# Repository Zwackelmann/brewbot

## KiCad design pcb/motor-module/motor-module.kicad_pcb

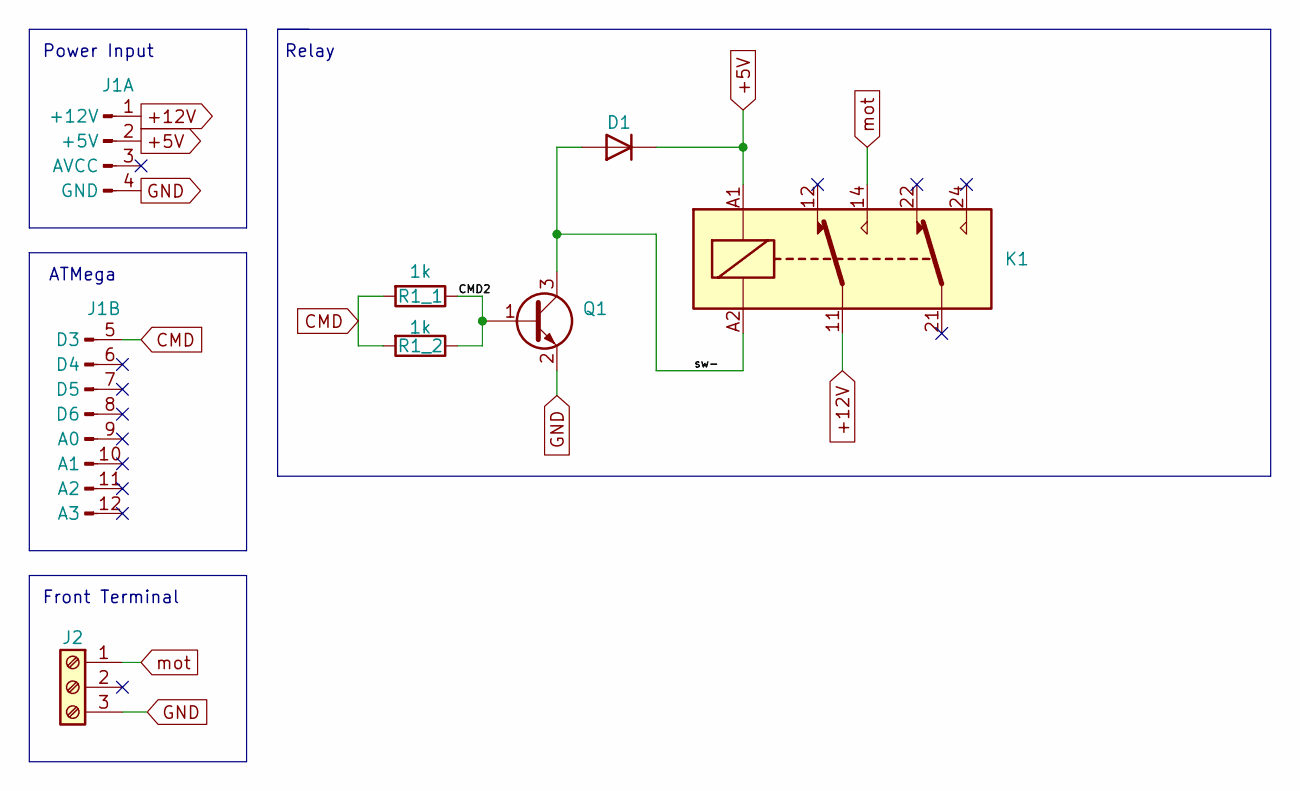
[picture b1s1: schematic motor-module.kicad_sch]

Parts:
D1: GS1A Gleichrichterdiode, 50 V, 1 A, DO-214AC/SMA; D_SMA
J1: Connector_male_4x8
J2: Screw_Terminal_01x03; Wago_734-163_1x03_P3.50mm_Horizontal
K1: AZ822-2C-5DSE Signal-Relais, 5 V DC, 2 A, 2 CO; Relay_DPDT_Finder_30.22
Q1: 2N 2222A SMD Bipolartransistor, NPN, 40V, 0,8A, 0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; SOT-23
R1_1, R1_2: 1k; R_0805_2012Metric

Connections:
+5V: D1.1 (K), J1.2 (+5V), K1.A1
+12V: J1.1 (+12V), K1.11
/CMD2: Q1.1 (B), R1_1.1, R1_2.1
/sw-: D1.2 (A), K1.A2, Q1.3 (C)
CMD: J1.5 (D3), R1_1.2, R1_2.2
GND: J1.4 (GND), J2.3, Q1.2 (E)
mot: J2.1, K1.14

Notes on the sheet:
ATMega
Power Input
Relay
Front Terminal

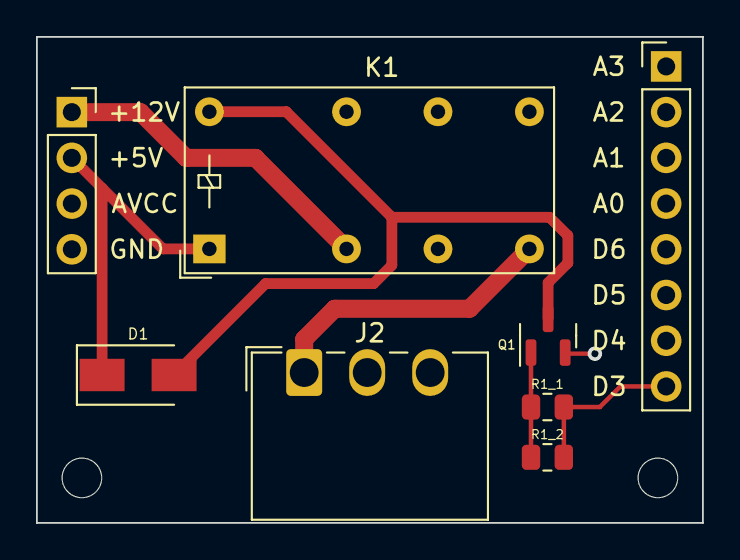
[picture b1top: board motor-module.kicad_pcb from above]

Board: 2 copper layers, 37.0 x 27.0 mm, 7 parts (0 on the bottom side), 7 nets.

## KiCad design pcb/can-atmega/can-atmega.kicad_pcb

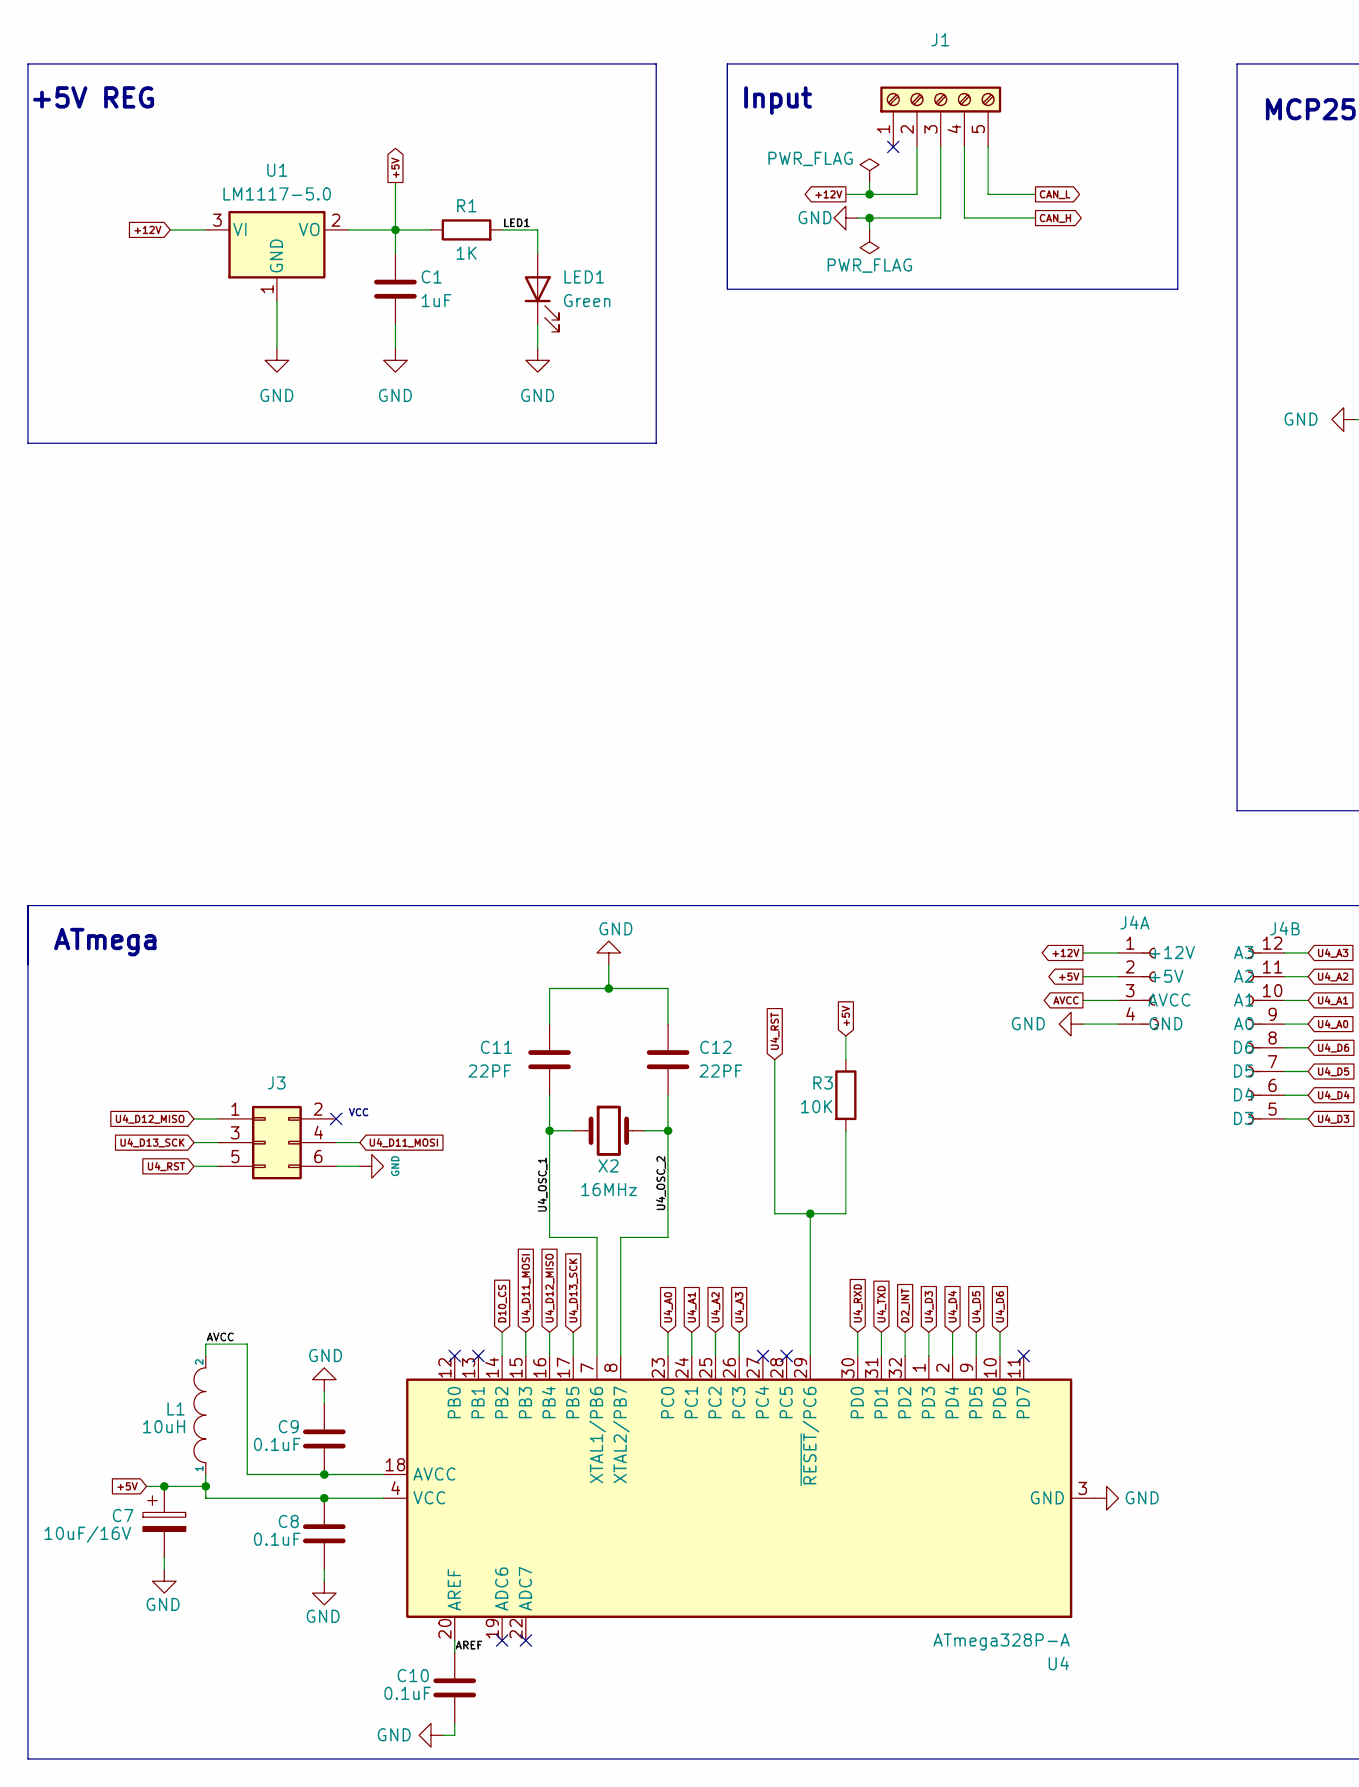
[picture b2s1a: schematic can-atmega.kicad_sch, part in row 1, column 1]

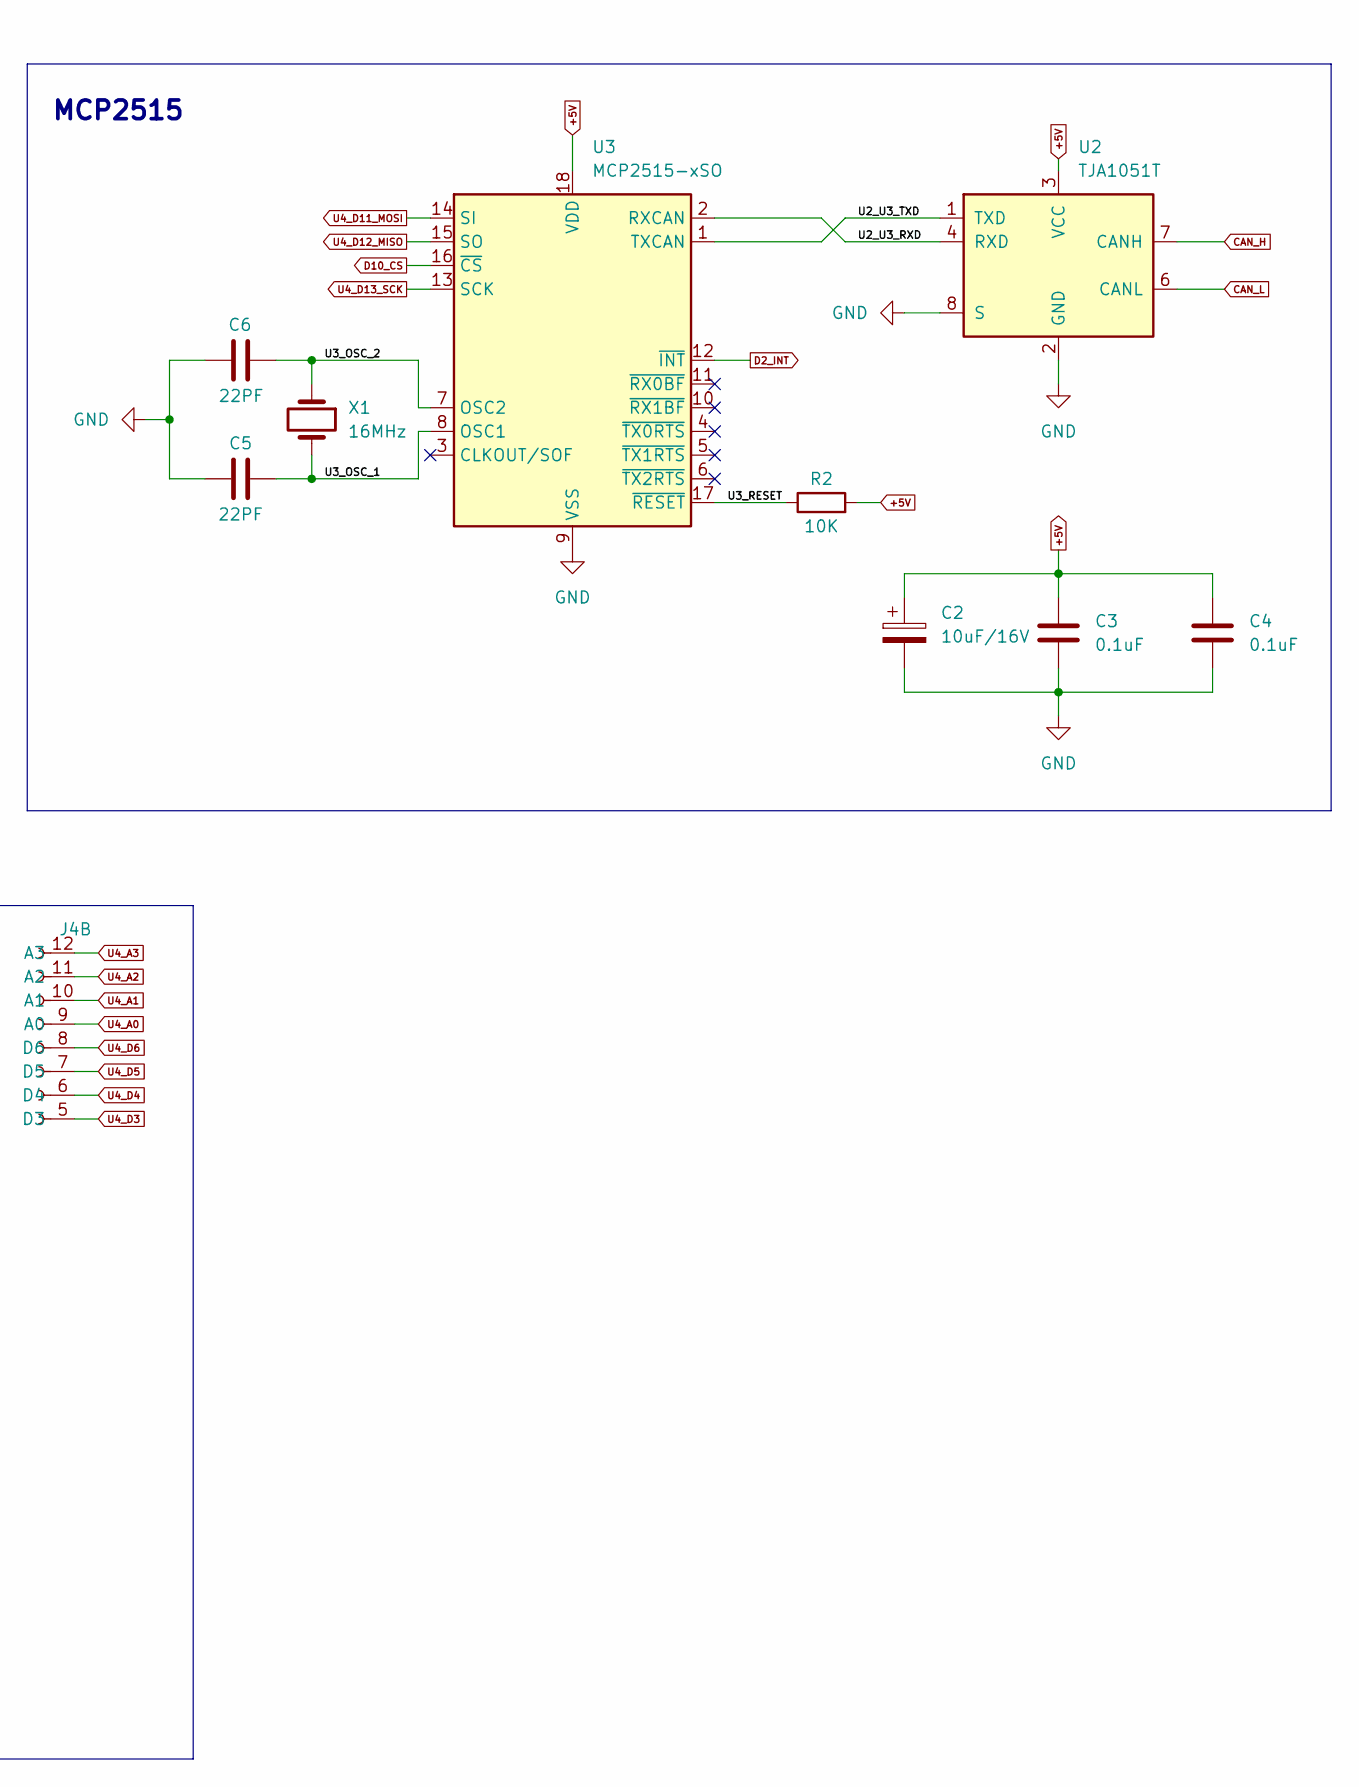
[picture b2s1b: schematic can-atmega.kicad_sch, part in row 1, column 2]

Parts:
C1: 1uF; C_1206_3216Metric
C2, C7: 10uF/16V; CP_EIA-3216-18_Kemet-A
C3, C4, C8, C9, C10: 0.1uF; C_1206_3216Metric
C5, C6, C11, C12: 22PF; C_1206_3216Metric
J1: Screw_Terminal_01x05; 4301207
J3: Conn_02x03_Odd_Even; IDC-Header_2x03_P2.54mm_Vertical
J4: Connector_female_4x8
L1: 10uH; L_Neosid_SMS-ME3010
LED1: Green; LED_0805_2012Metric
R1: 1K; R_0805_2012Metric
R2, R3: 10K; R_0805_2012Metric
U1: LM1117-5.0; SOT-223
U2: TJA1051T; SOIC-8_3.9x4.9mm_P1.27mm
U3: MCP2515-xSO; SOIC-18W_7.5x11.6mm_P1.27mm
U4: ATmega328P-A; TQFP-32_7x7mm_P0.8mm
X1, X2: 16MHz; Crystal_HC49-4H_Vertical

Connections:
+5V: C1.1, C2.1, C3.1, C4.1, C7.1, C8.1, J4.2 (+5V), L1.1, R1.1, R2.2, R3.1, U1.2 (VO), U1.4, U2.3 (VCC), U3.18 (VDD), U4.4 (VCC), U4.6 (VCC)
+12V: J1.2, J4.1 (+12V), U1.3 (VI)
/AREF: C10.2, U4.20 (AREF)
/LED1: LED1.2 (A), R1.2
/U2_U3_RXD: U2.4 (RXD), U3.2 (RXCAN)
/U2_U3_TXD: U2.1 (TXD), U3.1 (TXCAN)
/U3_OSC_1: C5.2, U3.8 (OSC1), X1.2
/U3_OSC_2: C6.2, U3.7 (OSC2), X1.1
/U3_RESET: R2.1, U3.17 (~RESET)
/U4_OSC_1: C11.1, U4.7 (XTAL1/PB6), X2.1
/U4_OSC_2: C12.2, U4.8 (XTAL2/PB7), X2.2
AVCC: C9.2, J4.3 (AVCC), L1.2, U4.18 (AVCC)
CAN_H: J1.4, U2.7 (CANH)
CAN_L: J1.5, U2.6 (CANL)
D2_INT: U3.12 (~INT), U4.32 (PD2)
D10_CS: U3.16 (~CS), U4.14 (PB2)
GND: C1.2, C2.2, C3.2, C4.2, C5.1, C6.1, C7.2, C8.2, C9.1, C10.1, C11.2, C12.1, J1.3, J3.6, J4.4 (GND), LED1.1 (K), U1.1 (GND), U2.2 (GND), U2.8 (S), U3.9 (VSS), U4.3 (GND), U4.5 (GND), U4.21 (GND)
U4_A0: J4.9 (A0), U4.23 (PC0)
U4_A1: J4.10 (A1), U4.24 (PC1)
U4_A2: J4.11 (A2), U4.25 (PC2)
U4_A3: J4.12 (A3), U4.26 (PC3)
U4_D3: J4.5 (D3), U4.1 (PD3)
U4_D4: J4.6 (D4), U4.2 (PD4)
U4_D5: J4.7 (D5), U4.9 (PD5)
U4_D6: J4.8 (D6), U4.10 (PD6)
U4_D11_MOSI: J3.4, U3.14 (SI), U4.15 (PB3)
U4_D12_MISO: J3.1, U3.15 (SO), U4.16 (PB4)
U4_D13_SCK: J3.3, U3.13 (SCK), U4.17 (PB5)
U4_RST: J3.5, R3.2, U4.29 (~RESET/PC6)
U4_RXD: U4.30 (PD0)
U4_TXD: U4.31 (PD1)

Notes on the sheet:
+5V REG
ATmega
MCP2515
VCC
Input

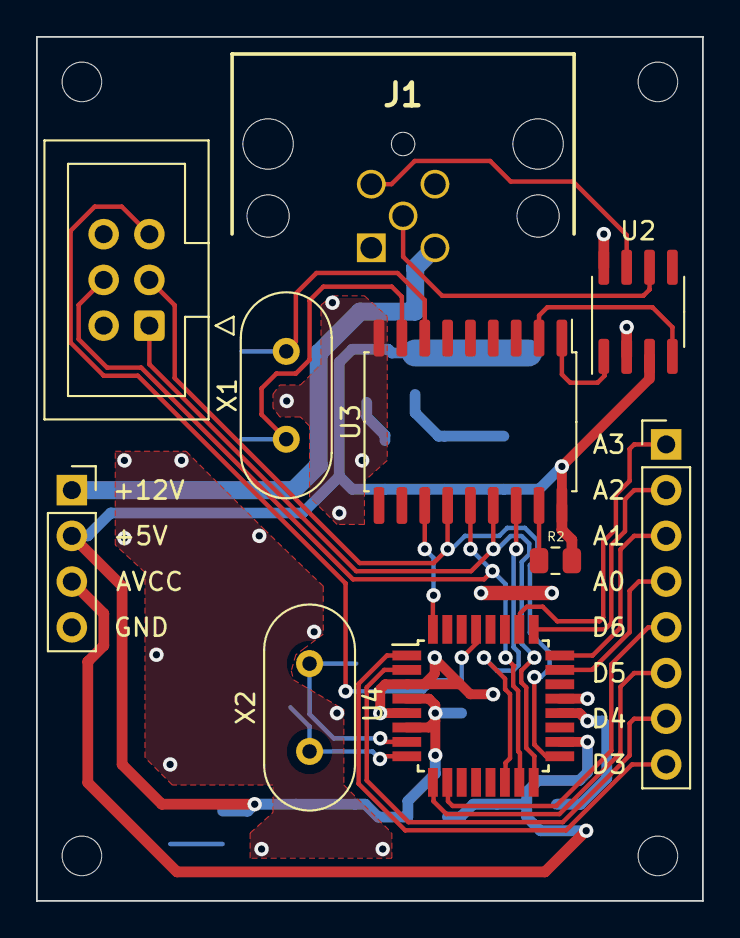
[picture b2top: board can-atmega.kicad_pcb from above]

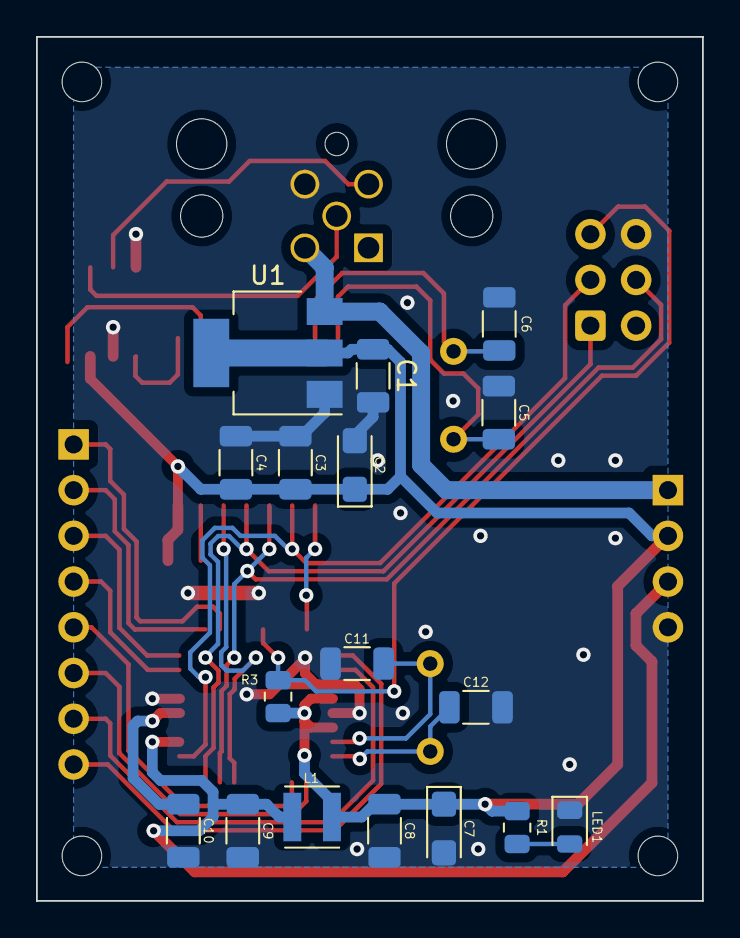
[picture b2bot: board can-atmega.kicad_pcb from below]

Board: 2 copper layers, 37.0 x 48.0 mm, 26 parts (17 on the bottom side), 29 nets.

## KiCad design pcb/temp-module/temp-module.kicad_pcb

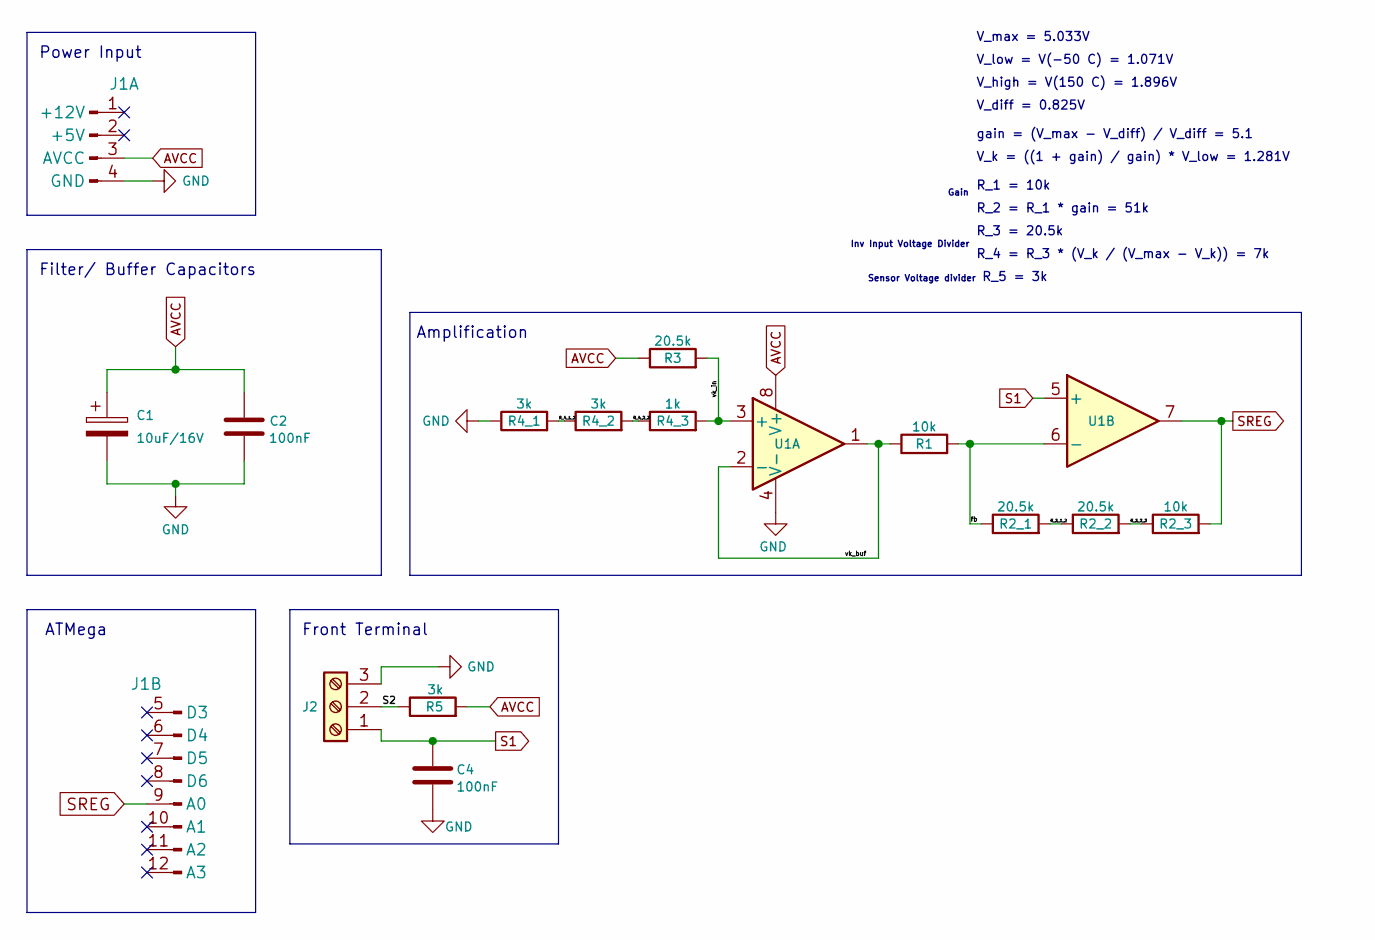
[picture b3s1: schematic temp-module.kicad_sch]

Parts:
C1: 10uF/16V; C_1206_3216Metric
C2, C4: 100nF; C_1206_3216Metric
J1: Connector_male_4x8
J2: Screw_Terminal_01x03; Wago_734-163_1x03_P3.50mm_Horizontal
R1, R2_3: 10k; R_0805_2012Metric
R2_1, R2_2, R3: 20.5k; R_0805_2012Metric
R4_1, R4_2, R5: 3k; R_0805_2012Metric
R4_3: 1k; R_0805_2012Metric
U1: MCP6002-xP; DIP-8_W7.62mm

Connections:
/R_2_1_2: R2_1.2, R2_2.1
/R_2_2_3: R2_2.2, R2_3.1
/R_4_1_2: R4_1.2, R4_2.1
/R_4_2_3: R4_2.2, R4_3.1
/S2: J2.2, R5.1
/fb: R1.2, R2_1.1, U1.6 (-)
/vk_buf: R1.1, U1.1, U1.2 (-)
/vk_in: R3.2, R4_3.2, U1.3 (+)
AVCC: C1.1, C2.1, J1.3 (AVCC), R3.1, R5.2, U1.8 (V+)
GND: C1.2, C2.2, C4.2, J1.4 (GND), J2.3, R4_1.1, U1.4 (V-)
S1: C4.1, J2.1, U1.5 (+)
SREG: J1.9 (A0), R2_3.2, U1.7

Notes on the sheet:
gain = (V_max - V_diff) / V_diff = 5.1
Inv Input Voltage Divider
Gain
V_high = V(150 C) = 1.896V
R_4 = R_3 * (V_k / (V_max - V_k)) = 7k
V_max = 5.033V
V_diff = 0.825V
Amplification
Front Terminal
Sensor Voltage divider
R_5 = 3k
Filter/ Buffer Capacitors
V_k = ((1 + gain) / gain) * V_low = 1.281V
ATMega
Power Input
V_low = V(-50 C) = 1.071V
R_2 = R_1 * gain = 51k
R_3 = 20.5k
R_1 = 10k

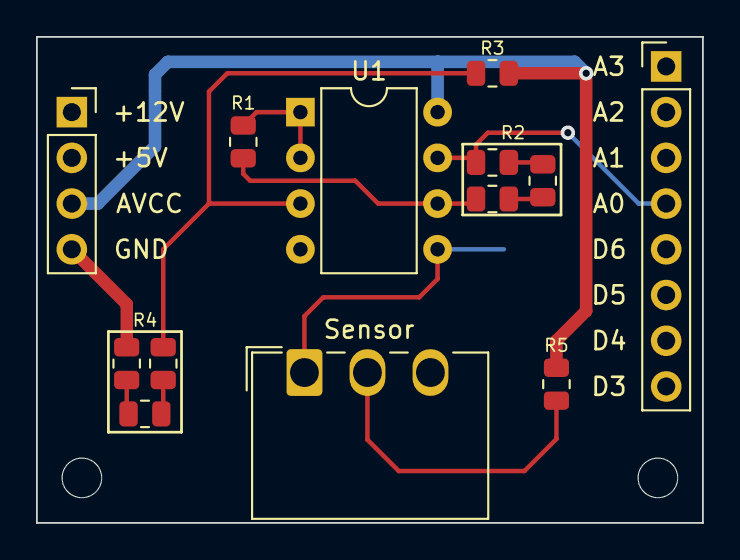
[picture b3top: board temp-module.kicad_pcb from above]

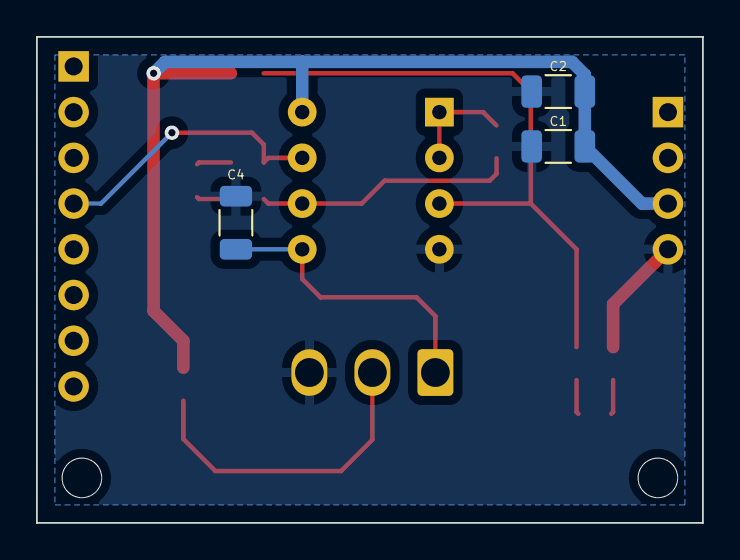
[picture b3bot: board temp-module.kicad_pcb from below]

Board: 2 copper layers, 37.0 x 27.0 mm, 15 parts (3 on the bottom side), 12 nets.

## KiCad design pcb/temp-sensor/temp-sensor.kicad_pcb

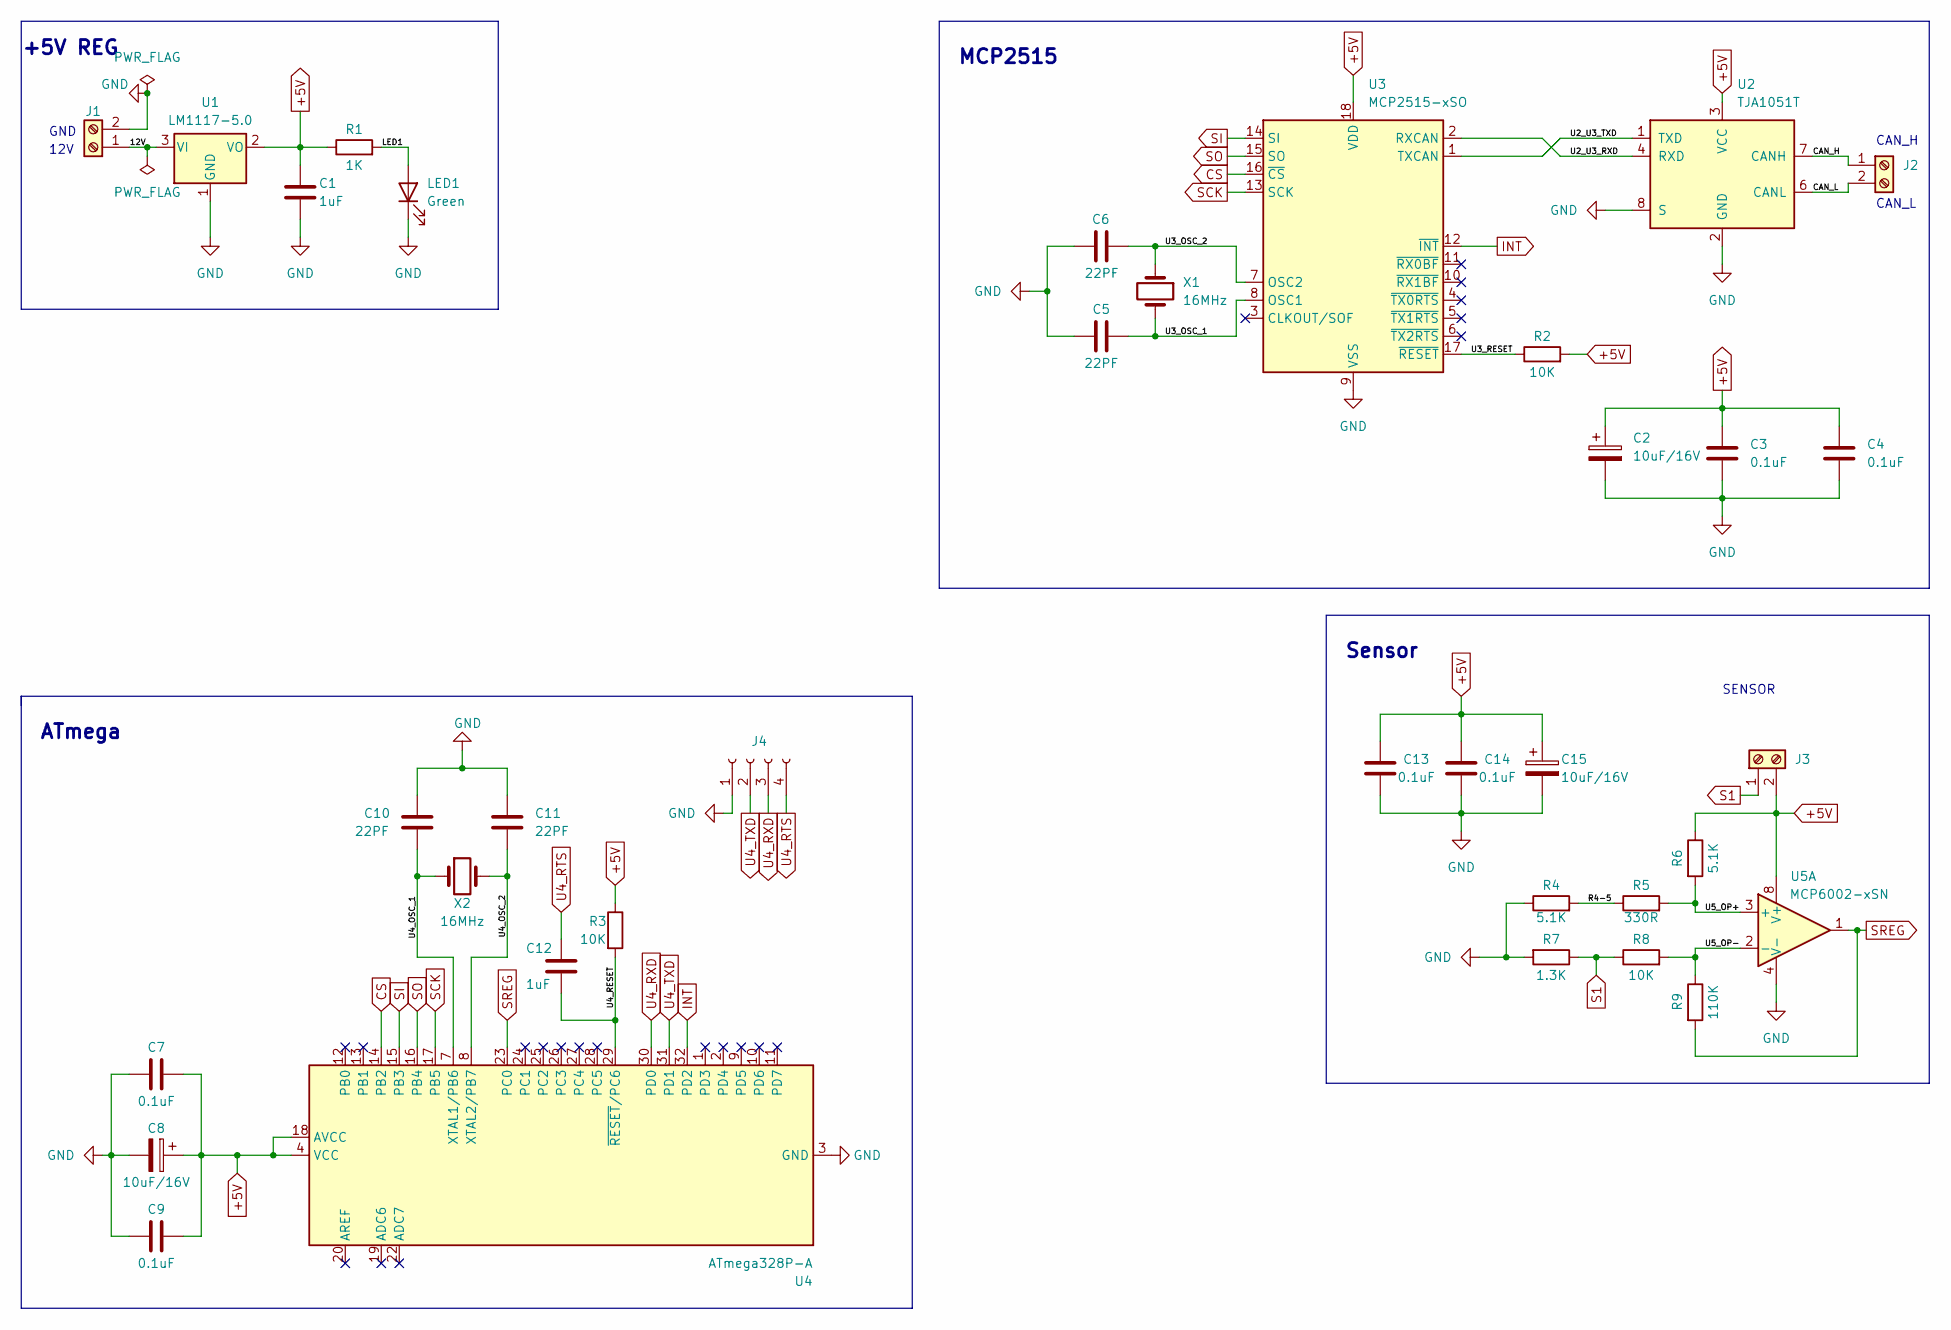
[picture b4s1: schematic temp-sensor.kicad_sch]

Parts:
C1, C12: 1uF; C_KEM_0805_2.0x1.25mm
C2, C8, C15: 10uF/16V; C_TAJ_3516_Bauform_A
C3, C4, C7, C9, C13, C14: 0.1uF; C_KEM_0805_2.0x1.25mm
C5, C6, C10, C11: 22PF; C_KEM_0805_2.0x1.25mm
J1, J2, J3: Screw_Terminal_01x02; TerminalBlock_bornier-2_P5.08mm
J4: Conn_01x04_Female; PinHeader_1x04_P2.54mm_Vertical
LED1: Green; LED_EL_0603_GR1_1608
R1: 1K; R_SPR-0603_1.6x0.8mm
R2, R3, R8: 10K; R_SPR-0603_1.6x0.8mm
R4, R6: 5.1K; R_SPR-0603_1.6x0.8mm
R5: 330R; R_SPR-0603_1.6x0.8mm
R7: 1.3K; R_SPR-0603_1.6x0.8mm
R9: 110K; R_SPR-0603_1.6x0.8mm
U1: LM1117-5.0; SOT-223
U2: TJA1051T; SOIC-8_3.9x4.9mm_P1.27mm
U3: MCP2515-xSO; SOIC-18W_7.5x11.6mm_P1.27mm
U4: ATmega328P-A; TQFP-32_7x7mm_P0.8mm
U5: MCP6002-xSN; DIP-8_W7.62mm
X1, X2: 16MHz; Crystal_HC49-4H_Vertical

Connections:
+5V: C1.1, C2.1, C3.1, C4.1, C7.1, C8.1, C9.1, C13.1, C14.2, C15.1, J3.2, R1.1, R2.2, R3.1, R6.1, U1.2 (VO), U2.3 (VCC), U3.18 (VDD), U4.4 (VCC), U4.6 (VCC), U4.18 (AVCC), U5.8 (V+)
/12V: J1.1, U1.3 (VI)
/CAN_H: J2.1, U2.7 (CANH)
/CAN_L: J2.2, U2.6 (CANL)
/LED1: LED1.2 (A), R1.2
/R4-5: R4.2, R5.1
/U2_U3_RXD: U2.4 (RXD), U3.2 (RXCAN)
/U2_U3_TXD: U2.1 (TXD), U3.1 (TXCAN)
/U3_OSC_1: C5.2, U3.8 (OSC1), X1.2
/U3_OSC_2: C6.2, U3.7 (OSC2), X1.1
/U3_RESET: R2.1, U3.17 (~RESET)
/U4_OSC_1: C10.1, U4.7 (XTAL1/PB6), X2.1
/U4_OSC_2: C11.2, U4.8 (XTAL2/PB7), X2.2
/U4_RESET: C12.2, R3.2, U4.29 (~RESET/PC6)
/U5_OP+: R5.2, R6.2, U5.3 (+)
/U5_OP-: R8.2, R9.1, U5.2 (-)
CS: U3.16 (~CS), U4.14 (PB2)
GND: C1.2, C2.2, C3.2, C4.2, C5.1, C6.1, C7.2, C8.2, C9.2, C10.2, C11.1, C13.2, C14.1, C15.2, J1.2, J4.1, LED1.1 (K), R4.1, R7.2, U1.1 (GND), U2.2 (GND), U2.8 (S), U3.9 (VSS), U4.3 (GND), U4.5 (GND), U4.21 (GND), U5.4 (V-)
INT: U3.12 (~INT), U4.32 (PD2)
S1: J3.1, R7.1, R8.1
SCK: U3.13 (SCK), U4.17 (PB5)
SI: U3.14 (SI), U4.15 (PB3)
SO: U3.15 (SO), U4.16 (PB4)
SREG: R9.2, U4.23 (PC0), U5.1
U4_RTS: C12.1, J4.4
U4_RXD: J4.3, U4.30 (PD0)
U4_TXD: J4.2, U4.31 (PD1)

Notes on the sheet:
CAN_H
+5V REG
12V
Sensor
CAN_L
ATmega
MCP2515
GND
SENSOR

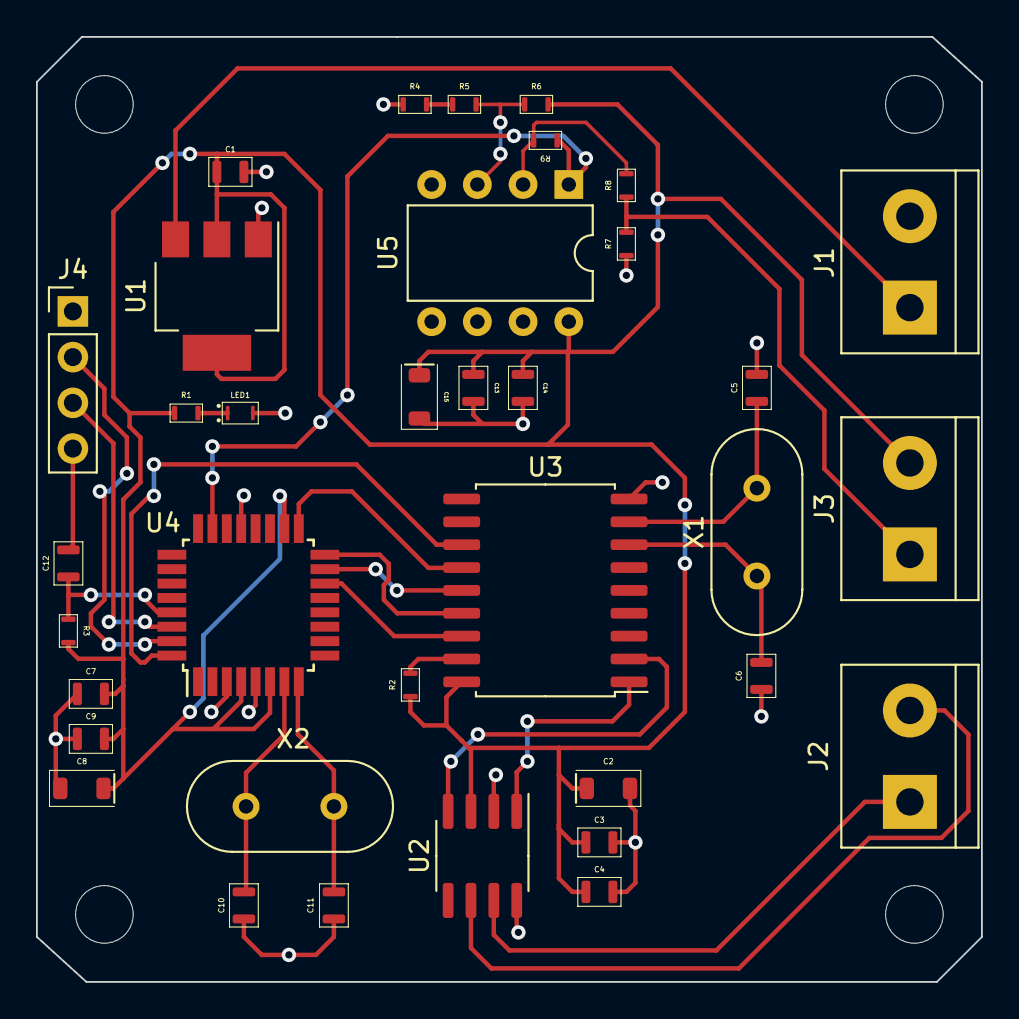
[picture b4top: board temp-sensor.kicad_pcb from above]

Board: 2 copper layers, 52.5 x 52.5 mm, 36 parts (0 on the bottom side), 27 nets.

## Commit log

2022-08-31 init
2022-10-19 fundamental frontend
2023-01-07 new frontend
2023-02-07 added frontend
2023-02-14 frontend refactor
2024-01-06 added pcb and 3d files
2024-01-07 modified pcbs
2024-01-14 motor module
2024-01-15 update pcb
2024-03-30 added AVRISP adapter to pcb
2024-04-14 m12 plug; j1939 transition
2024-04-16 j1939 send and receive
2024-06-10 can based backend first steps
2024-07-14 new async unicorn backend
2024-07-20 can nodes send states now
2024-07-21 better mocking
2024-07-21 minimal functional frontend
2024-07-22 formatting; documentation
2024-09-08 added pid
2024-09-08 renaming
2024-09-08 refactor
2024-10-20 temp-calibrate
2024-10-20 calibrate plots
2024-10-30 new temp module
2024-10-30 plots
2025-01-10 board updates
2025-02-02 refactored config and can
2025-02-16 node based backend refactored
2025-06-14 assembly
2025-06-14 updated pcb
2025-06-15 controller test
2025-07-03 pcb update
2025-07-05 pcb fab 2025-07-04
2025-07-07 can env
2025-07-07 task status route
2025-08-07 generated dbc files
2025-08-17 started j1939 generated lib
2025-08-17 j1939 manually generated code ready
2025-08-17 test on can node
